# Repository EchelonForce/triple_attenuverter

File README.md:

# Triple Attenuverter

This is an attenuverter (attenuate, invert, offset) module for Eurorack synthesizers.

Full write up here: https://www.robotdialogs.com/2022/09/eurorack-triple-attenuverter.html

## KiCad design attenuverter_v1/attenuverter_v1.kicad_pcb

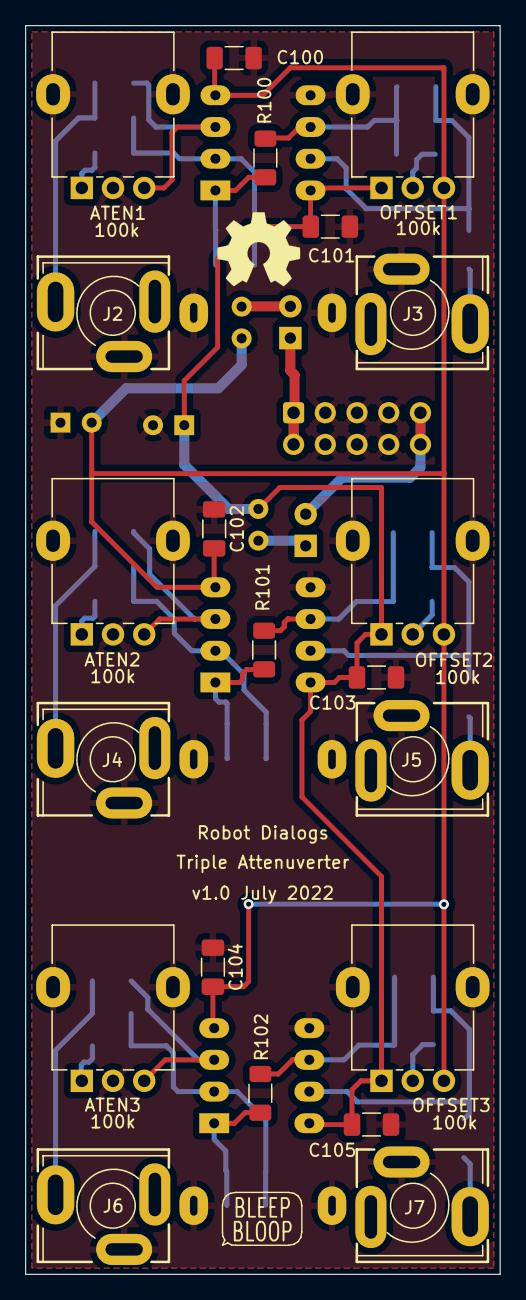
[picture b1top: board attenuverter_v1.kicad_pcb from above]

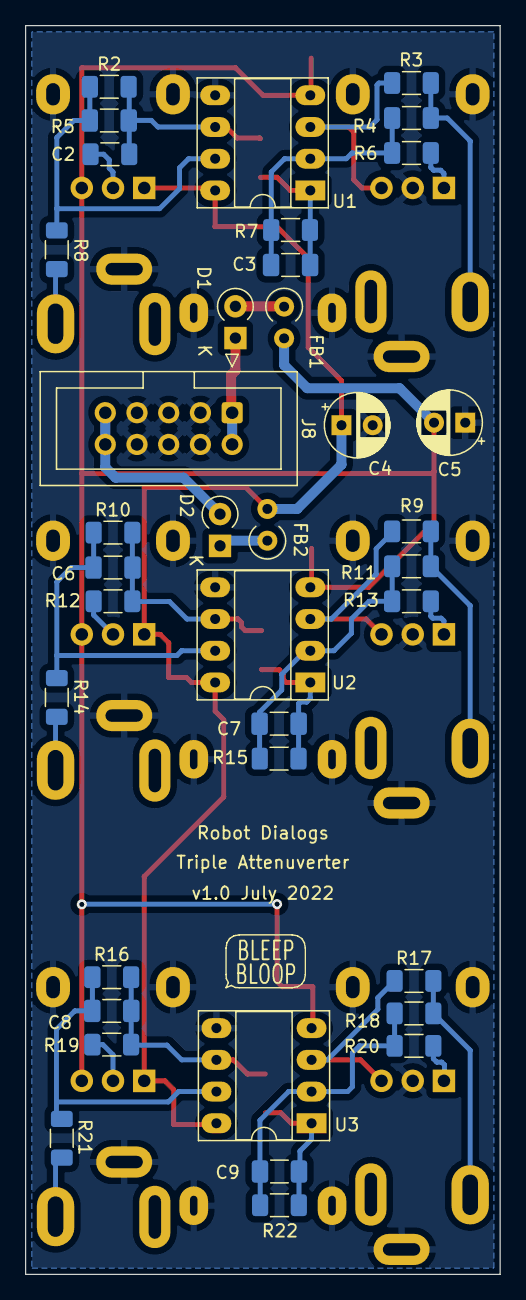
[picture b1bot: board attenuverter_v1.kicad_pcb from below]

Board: 2 copper layers, 38.0 x 100.0 mm, 61 parts (37 on the bottom side), 34 nets.

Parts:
ATEN1, ATEN2, ATEN3: 100k; Potentiometer_Alpha_RD901F-40-00D_Single_Vertical_w_3d
C2, C3, C6, C7, C8, C9: 10pF; C_1206_3216Metric_Pad1.33x1.80mm_HandSolder
C4, C5: 100uF; CP_Radial_D5.0mm_P2.50mm
C100, C101, C102, C103, C104, C105: 10nF; C_1206_3216Metric_Pad1.33x1.80mm_HandSolder
D1, D2: D; D_A-405_P2.54mm_Vertical_KathodeUp
FB1, FB2: FerriteBead; L_Axial_L6.6mm_D2.7mm_P2.54mm_Vertical_Vishay_IM-2
J2, J3, J4, J5, J6, J7: AudioJack2_SwitchT; Jack_3.5mm_MJ-355W_and_PJ398SM_Vertical
J8: Conn_02x05_Odd_Even; IDC-Header_2x05_P2.54mm_Vertical
LOGO100: Logo_Open_Hardware_Small; OSHW-Symbol_6.7x6mm_SilkScreen
LOGO101: logo1; Logo2
LOGO102: logo1; Logo1
OFFSET1, OFFSET2, OFFSET3: 100k; Potentiometer_Alpha_RD901F-40-00D_Single_Vertical_w_3d
R2, R5, R10, R12, R16, R19, R100, R101, R102: 10k; R_1206_3216Metric_Pad1.30x1.75mm_HandSolder
R3, R4, R7, R9, R11, R15, R17, R18, R22: 100k; R_1206_3216Metric_Pad1.30x1.75mm_HandSolder
R6, R13, R20: 47k; R_1206_3216Metric_Pad1.30x1.75mm_HandSolder
R8, R14, R21: 1k; R_1206_3216Metric_Pad1.30x1.75mm_HandSolder
U1, U2, U3: TL072; DIP-8_W7.62mm_Socket_LongPads

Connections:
+12V: C4.1, C101.1, C103.1, C105.1, FB2.2, OFFSET1.1, OFFSET2.1, OFFSET3.1, U1.8 (V+), U2.8 (V+), U3.8 (V+)
+12VA: D2.2 (A), J8.9, J8.10
-12V: C5.2, C100.2, C102.2, C104.2, FB1.2, OFFSET1.3, OFFSET2.3, OFFSET3.3, U1.4 (V-), U2.4 (V-), U3.4 (V-)
-12VA: D1.1 (K), J8.1, J8.2
/Attenuverter Block1/IN: J4.T, R9.2, R11.1
/Attenuverter Block1/OUT: J5.T, R14.1
/Attenuverter Block2/IN: J6.T, R17.2, R18.1
/Attenuverter Block2/OUT: J7.T, R21.1
/Attenuverter Block/IN: J2.T, R3.2, R4.1
/Attenuverter Block/OUT: J3.T, R8.1
GND: ATEN1.2, ATEN1.MP (MountPin), ATEN2.2, ATEN2.MP (MountPin), ATEN3.2, ATEN3.MP (MountPin), C4.2, C5.1, C100.1, C101.2, C102.1, C103.2, C104.1, C105.2, J2.S, J3.S, J4.S, J5.S, J6.S, J7.S, J8.3, J8.4, J8.5, J8.6, J8.7, J8.8, OFFSET1.MP (MountPin), OFFSET2.MP (MountPin), OFFSET3.MP (MountPin), U1.5 (+), U2.5 (+), U3.5 (+)
unnamed: ATEN1.1, R6.2
unnamed: ATEN1.3, R3.1, U1.3 (+)
unnamed: ATEN2.1, R13.2
unnamed: ATEN2.3, R9.1, U2.3 (+)
unnamed: ATEN3.1, R20.2
unnamed: ATEN3.3, R17.1, U3.3 (+)
unnamed: C2.1, R2.2, R5.2, R100.2, U1.6 (-)
unnamed: C2.2, R2.1, R8.2, U1.7
unnamed: C3.1, R4.2, R6.1, R7.1, U1.2 (-)
unnamed: C3.2, R7.2, R100.1, U1.1
unnamed: C6.1, R10.2, R12.2, R101.2, U2.6 (-)
unnamed: C6.2, R10.1, R14.2, U2.7
unnamed: C7.1, R11.2, R13.1, R15.1, U2.2 (-)
unnamed: C7.2, R15.2, R101.1, U2.1
unnamed: C8.1, R16.2, R19.2, R102.2, U3.6 (-)
unnamed: C8.2, R16.1, R21.2, U3.7
unnamed: C9.1, R18.2, R20.1, R22.1, U3.2 (-)
unnamed: C9.2, R22.2, R102.1, U3.1
unnamed: D1.2 (A), FB1.1
unnamed: D2.1 (K), FB2.1
unnamed: OFFSET1.2, R5.1
unnamed: OFFSET2.2, R12.1
unnamed: OFFSET3.2, R19.1

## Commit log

2022-07-05 Initial commit with .gitignore
2022-07-05 Schematic and initial layout, no routing
2022-07-05 First pass routing done
2022-07-05 Silkscreen cleanup and labeling
2022-07-05 Geographic rename
2022-07-27 Panelized version of v1 and Notes.txt
2022-07-27 Front Panel v1 CAD
2022-07-27 Front Panel v1.1 CAD
2022-09-04 Add readme
2022-09-04 Add schematic pdf
